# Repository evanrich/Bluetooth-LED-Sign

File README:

# Bluetooth LED Sign - Control Sure 3216 displays from your computer/phone via Bluetooth

The Bluetooth sign project started out originally from me wanting a wireless sign I could put in my car to tell drivers to get off my ass when they were following too close.    It started as just a daughter card that was shaped to connect directly to the back of a Sure 3216 (3mm) display.  I then wanted to be able to have a much larger display, and instead of buying 3216 boards at $24+ plus shipping, I went about designing the equivelent of 3x 3216 boards. 

The project has many uses, from digital cube/office name or status signs (out of office?) to vehicle/store signs.

**Source code**

* https://github.com/evanrich/Bluetooth-LED-Sign

**Licensing**<br />
<br /><span xmlns:dct="http://purl.org/dc/terms/" property="dct:title">Bluetooth LED Sign</span> by <a xmlns:cc="http://creativecommons.org/ns#" href="https://github.com/evanrich/Bluetooth-LED-Sign" property="cc:attributionName" rel="cc:attributionURL">Evan Richardson</a> is licensed under a <a rel="license" href="http://creativecommons.org/licenses/by-sa/3.0/">Creative Commons Attribution-ShareAlike 3.0 Unported License</a>.<br />Based on a work at <a xmlns:dct="http://purl.org/dc/terms/" href="https://code.google.com/p/ht1632c/" rel="dct:source">code.google.com</a>.

**Features**

* Small Size: 54x39mm ( 2.13" x 1.54")
* Custom LED Board is 15.15"3.20"
* Multiple mounting options: Controller plugs directly into back of Sure 3216 or custom 9616 boards
* Low Power: Controller operates around 50-80mA (needs to be tested) with a 2000mAh battery it can run >4 hours on single charge
* Wireless: BLUETOOTH!!  works up to 30+ feet away
* Charges/Runs via USB port (500mA only, 12V wall plug option being added)
* Fuel Guage IC has been added to allow reporting/displaying of remaining capacity (Code needs to be added however)
* Android and VB.NET apps can both control message color and speed, as well as looping the message until a new message is sent.
* Android: Voice Control - enter messages using your voice
* Android: History - Resend any of the last recently used messages by taping on it and hitting send.

**Known issues**

* Android:  If phone is in one orientation (Horizontal/Vertical) and you rotate your phone, it will dissconnect from the bluetooth module.  This is due to destroying and recreating the view, and therefore the bluetooth connection.  Need to figure how to fix this, or not allow rotation.
* New Arduino 1.0 code will not work with more than 2 displays
* Old Arduino 0023 code is slow when using text scaling (2 instead of 1)
* Android: If a Repeat is issued to the display, it will loop the text until a new message is sent.
* VB.NET: If a repeat and color change are issued, the display will not stop repeating until a new color is sent.

**To-Do**

* Develop some sort of user guide/documentation
* Finalize BOM
* Write Fuel Guage code to allow transmission or display of remaining battery capacity
* Prototype 96x16 board(Currently routing board traces)
* Confirm board/schematic for controller (device is 1/2 the size the first prototype was)
* Find or develop tool to allow updating firmware on the board (USB parts are there, so new firmware updates can be sent out to users)
* Other stuff

**Questions/Support**

* Original library/Sure 3216 information on Arduino.cc Forums @ [http://arduino.cc/forum/index.php/board,6.0.html](http://arduino.cc)

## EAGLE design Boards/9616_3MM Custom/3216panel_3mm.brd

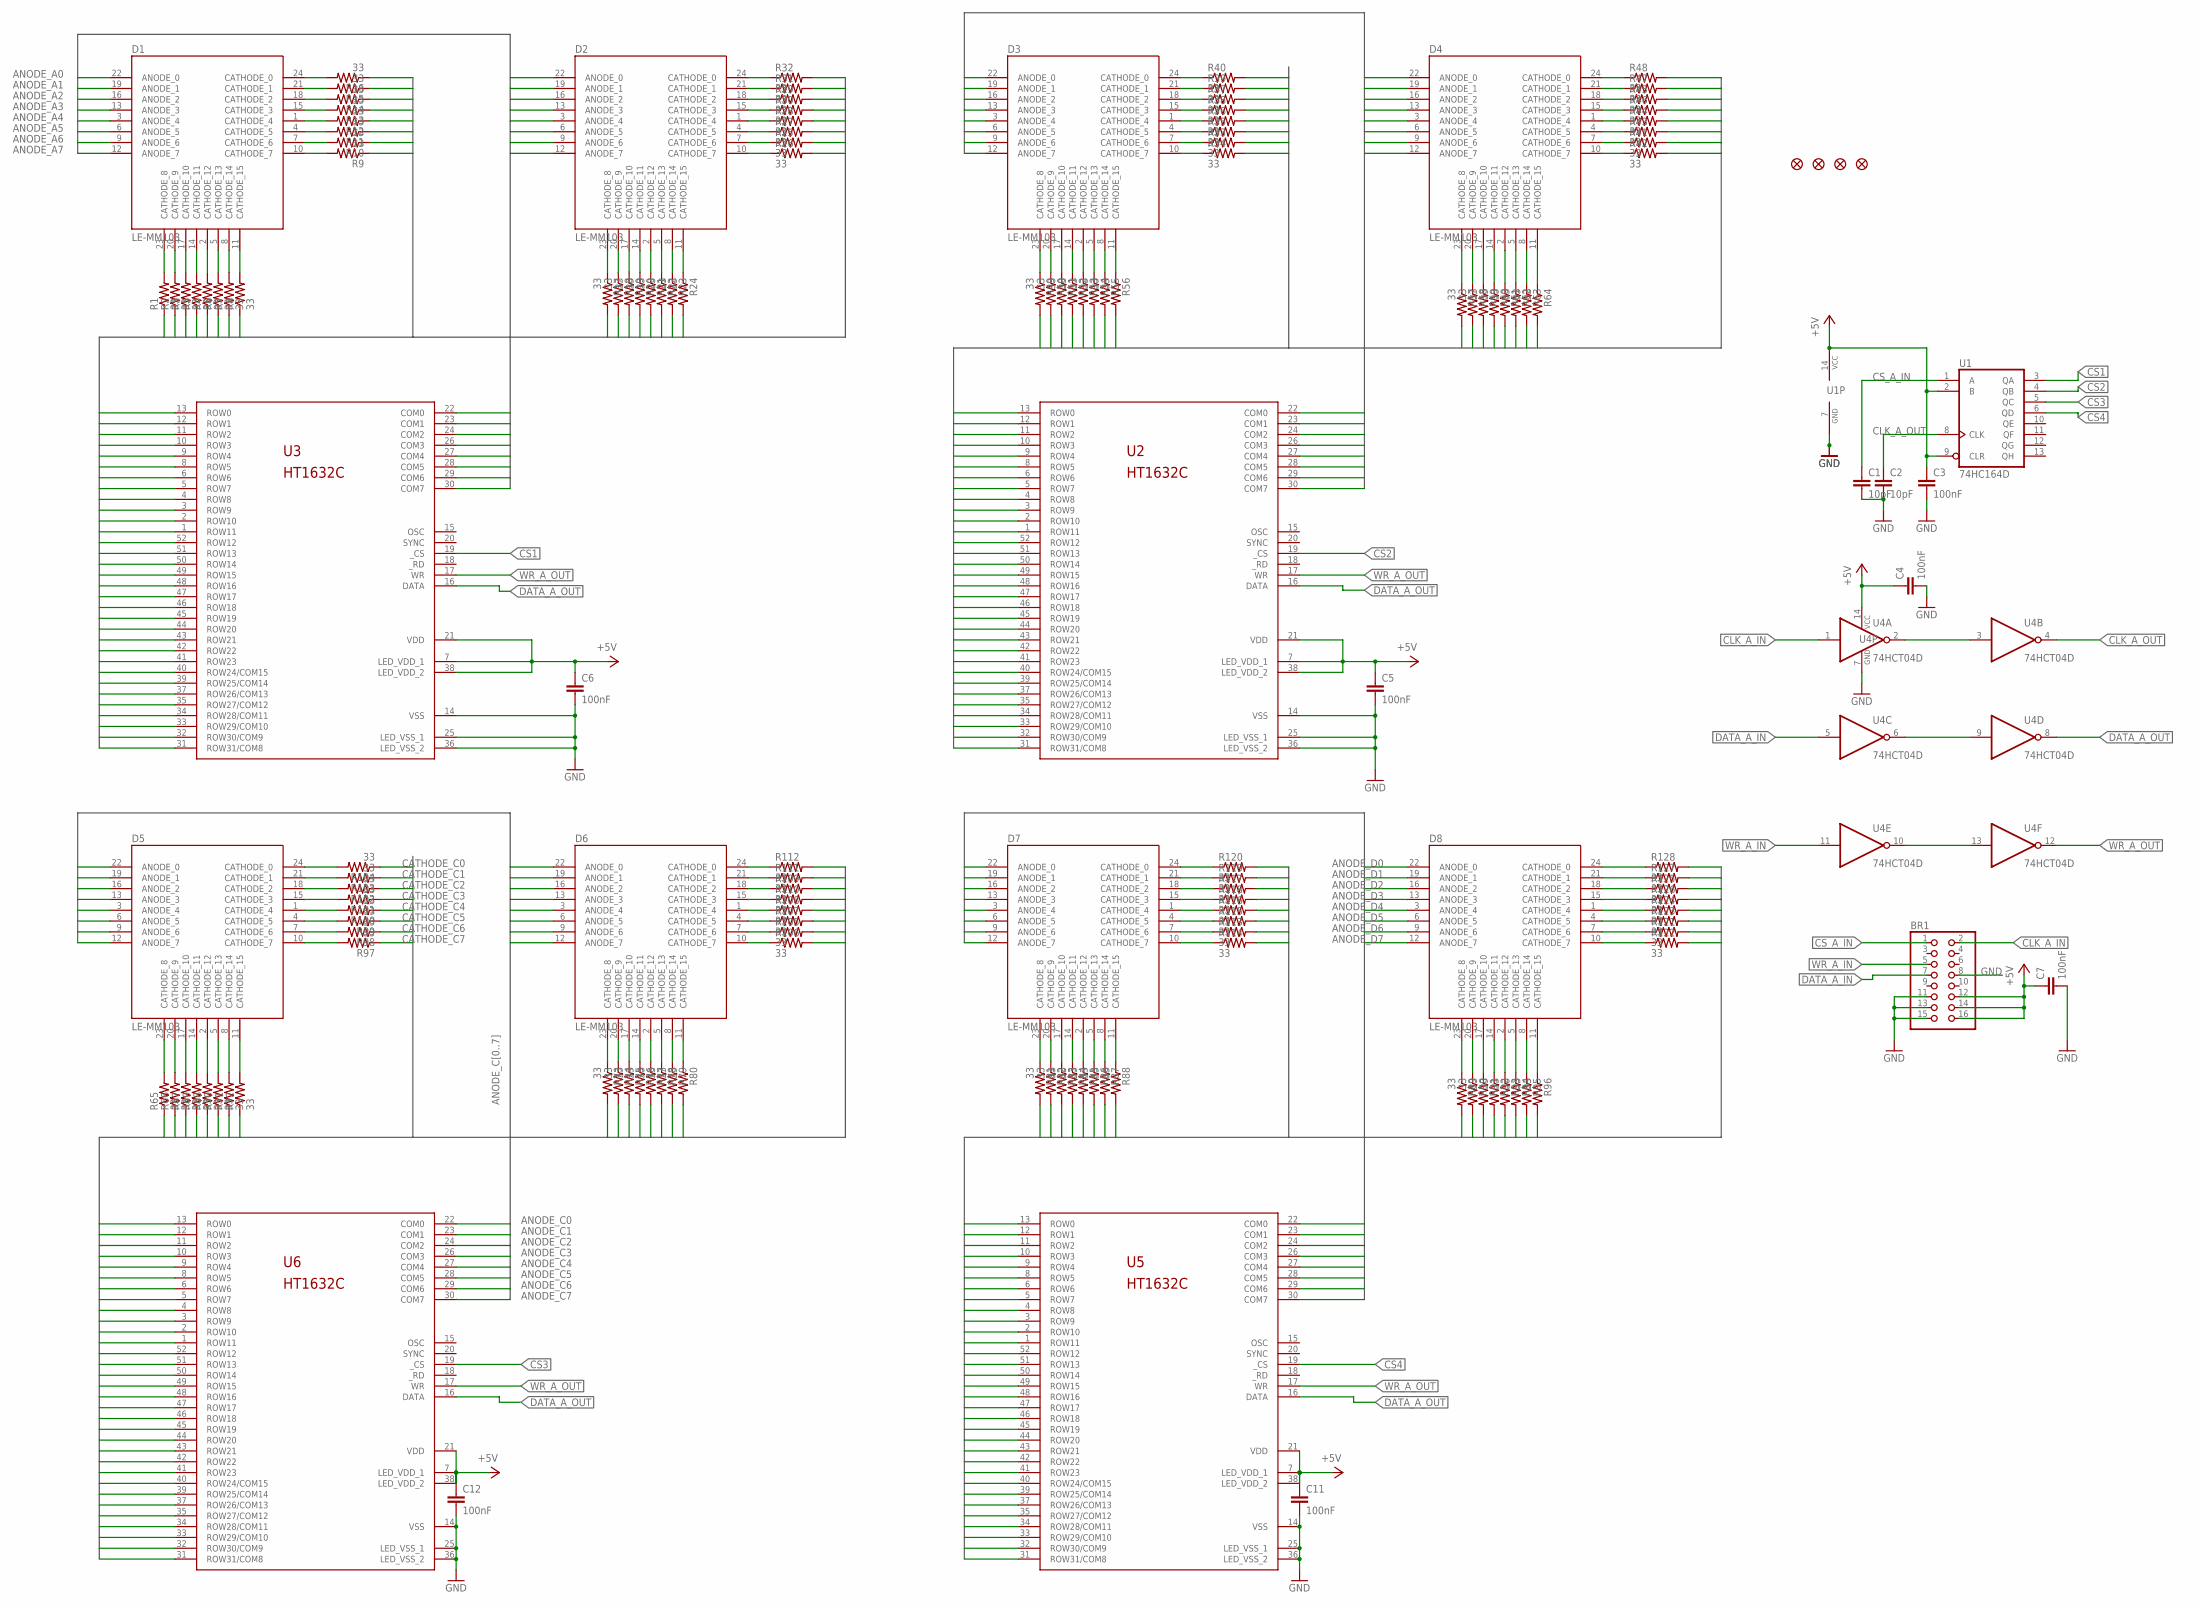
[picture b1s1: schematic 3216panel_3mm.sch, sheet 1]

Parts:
BR1: PINHD-2X8; 2X08
C1, C2: 10pF; 0805
C3, C4, C5, C6, C7, C11, C12: 100nF; 0805
D1, D2, D3, D4, D5, D6, D7, D8: LE-MM103; 8X8_3MM_LED_MATRIX
JP1, JP2, JP3, JP4: FIDUCIAL1X2.5; FIDUCIAL-1X2.5
R1, R2, R3, R4, R5, R6, R7, R8, R9, R10, R11, R12, R13, R14, R15, R16, R17, R18, R19, R20, R21, R22, R23, R24, R25, R26, R27, R28, R29, R30, R31, R32, R33, R34, R35, R36, R37, R38, R39, R40, R41, R42, R43, R44, R45, R46, R47, R48, R49, R50, R51, R52, R53, R54, R55, R56, R57, R58, R59, R60, R61, R62, R63, R64, R65, R66, R67, R68, R69, R70, R71, R72, R73, R74, R75, R76, R77, R78, R79, R80, R81, R82, R83, R84, R85, R86, R87, R88, R89, R90, R91, R92, R93, R94, R95, R96, R97, R98, R99, R100, R101, R102, R103, R104, R105, R106, R107, R108, R109, R110, R111, R112, R113, R114, R115, R116, R117, R118, R119, R120, R121, R122, R123, R124, R125, R126, R127, R128: 33; 0805
U1: 74HC164D; SO14
U2, U3, U5, U6: HT1632C; QFP52
U4: 74HCT04D; SO14

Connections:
+5V: BR1.12, BR1.14, BR1.16, C3.1, C4.1, C5.1, C6.1, C7.1, C11.1, C12.1, U1.2 (B), U1.9 (CLR), U1.14 (VCC), U2.7 (LED_VDD_1), U2.21 (VDD), U2.38 (LED_VDD_2), U3.7 (LED_VDD_1), U3.21 (VDD), U3.38 (LED_VDD_2), U4.14 (VCC), U5.7 (LED_VDD_1), U5.21 (VDD), U5.38 (LED_VDD_2), U6.7 (LED_VDD_1), U6.21 (VDD), U6.38 (LED_VDD_2); also elsewhere on the board
ANODE_A0: D1.22 (ANODE_0), D2.22 (ANODE_0), U3.22 (COM0)
ANODE_A1: D1.19 (ANODE_1), D2.19 (ANODE_1), U3.23 (COM1)
ANODE_A2: D1.16 (ANODE_2), D2.16 (ANODE_2), U3.24 (COM2)
ANODE_A3: D1.13 (ANODE_3), D2.13 (ANODE_3), U3.26 (COM3)
ANODE_A4: D1.3 (ANODE_4), D2.3 (ANODE_4), U3.27 (COM4)
ANODE_A5: D1.6 (ANODE_5), D2.6 (ANODE_5), U3.28 (COM5)
ANODE_A6: D1.9 (ANODE_6), D2.9 (ANODE_6), U3.29 (COM6)
ANODE_A7: D1.12 (ANODE_7), D2.12 (ANODE_7), U3.30 (COM7)
ANODE_B0: D3.22 (ANODE_0), D4.22 (ANODE_0), U2.22 (COM0)
ANODE_B1: D3.19 (ANODE_1), D4.19 (ANODE_1), U2.23 (COM1)
ANODE_B2: D3.16 (ANODE_2), D4.16 (ANODE_2), U2.24 (COM2)
ANODE_B3: D3.13 (ANODE_3), D4.13 (ANODE_3), U2.26 (COM3)
ANODE_B4: D3.3 (ANODE_4), D4.3 (ANODE_4), U2.27 (COM4)
ANODE_B5: D3.6 (ANODE_5), D4.6 (ANODE_5), U2.28 (COM5)
ANODE_B6: D3.9 (ANODE_6), D4.9 (ANODE_6), U2.29 (COM6)
ANODE_B7: D3.12 (ANODE_7), D4.12 (ANODE_7), U2.30 (COM7)
ANODE_C0: D5.22 (ANODE_0), D6.22 (ANODE_0), U6.22 (COM0)
ANODE_C1: D5.19 (ANODE_1), D6.19 (ANODE_1), U6.23 (COM1)
ANODE_C2: D5.16 (ANODE_2), D6.16 (ANODE_2), U6.24 (COM2)
ANODE_C3: D5.13 (ANODE_3), D6.13 (ANODE_3), U6.26 (COM3)
ANODE_C4: D5.3 (ANODE_4), D6.3 (ANODE_4), U6.27 (COM4)
ANODE_C5: D5.6 (ANODE_5), D6.6 (ANODE_5), U6.28 (COM5)
ANODE_C6: D5.9 (ANODE_6), D6.9 (ANODE_6), U6.29 (COM6)
ANODE_C7: D5.12 (ANODE_7), D6.12 (ANODE_7), U6.30 (COM7)
ANODE_D0: D7.22 (ANODE_0), D8.22 (ANODE_0), U5.22 (COM0)
ANODE_D1: D7.19 (ANODE_1), D8.19 (ANODE_1), U5.23 (COM1)
ANODE_D2: D7.16 (ANODE_2), D8.16 (ANODE_2), U5.24 (COM2)
ANODE_D3: D7.13 (ANODE_3), D8.13 (ANODE_3), U5.26 (COM3)
ANODE_D4: D7.3 (ANODE_4), D8.3 (ANODE_4), U5.27 (COM4)
ANODE_D5: D7.6 (ANODE_5), D8.6 (ANODE_5), U5.28 (COM5)
ANODE_D6: D7.9 (ANODE_6), D8.9 (ANODE_6), U5.29 (COM6)
ANODE_D7: D7.12 (ANODE_7), D8.12 (ANODE_7), U5.30 (COM7)
CATHODE_A0: R16.1, U3.13 (ROW0)
CATHODE_A1: R15.1, U3.12 (ROW1)
CATHODE_A2: R14.1, U3.11 (ROW2)
CATHODE_A3: R13.1, U3.10 (ROW3)
CATHODE_A4: R12.1, U3.9 (ROW4)
CATHODE_A5: R11.1, U3.8 (ROW5)
CATHODE_A6: R10.1, U3.6 (ROW6)
CATHODE_A7: R9.1, U3.5 (ROW7)
CATHODE_A8: R32.2, U3.4 (ROW8)
CATHODE_A9: R31.2, U3.3 (ROW9)
CATHODE_A10: R29.2, U3.2 (ROW10)
CATHODE_A11: R30.2, U3.1 (ROW11)
CATHODE_A12: R28.2, U3.52 (ROW12)
CATHODE_A13: R27.2, U3.51 (ROW13)
CATHODE_A14: R25.2, U3.50 (ROW14)
CATHODE_A15: R26.2, U3.49 (ROW15)
CATHODE_A16: R1.1, U3.48 (ROW16)
CATHODE_A17: R2.1, U3.47 (ROW17)
CATHODE_A18: R3.1, U3.46 (ROW18)
CATHODE_A19: R5.1, U3.45 (ROW19)
CATHODE_A20: R4.1, U3.44 (ROW20)
CATHODE_A21: R6.1, U3.43 (ROW21)
CATHODE_A22: R7.1, U3.42 (ROW22)
CATHODE_A23: R8.1, U3.41 (ROW23)
CATHODE_A24: R17.2, U3.40 (ROW24/COM15)
CATHODE_A25: R18.2, U3.39 (ROW25/COM14)
CATHODE_A26: R19.2, U3.37 (ROW26/COM13)
CATHODE_A27: R20.2, U3.35 (ROW27/COM12)
CATHODE_A28: R21.2, U3.34 (ROW28/COM11)
CATHODE_A29: R22.2, U3.33 (ROW29/COM10)
CATHODE_A30: R23.2, U3.32 (ROW30/COM9)
CATHODE_A31: R24.2, U3.31 (ROW31/COM8)
CATHODE_B0: R40.2, U2.13 (ROW0)
CATHODE_B1: R39.2, U2.12 (ROW1)
CATHODE_B2: R37.2, U2.11 (ROW2)
CATHODE_B3: R38.2, U2.10 (ROW3)
CATHODE_B4: R36.2, U2.9 (ROW4)
CATHODE_B5: R35.2, U2.8 (ROW5)
CATHODE_B6: R33.2, U2.6 (ROW6)
CATHODE_B7: R34.2, U2.5 (ROW7)
CATHODE_B8: R48.2, U2.4 (ROW8)
CATHODE_B9: R47.2, U2.3 (ROW9)
CATHODE_B10: R45.2, U2.2 (ROW10)
CATHODE_B11: R46.2, U2.1 (ROW11)
CATHODE_B12: R44.2, U2.52 (ROW12)
CATHODE_B13: R43.2, U2.51 (ROW13)
CATHODE_B14: R41.2, U2.50 (ROW14)
CATHODE_B15: R42.2, U2.49 (ROW15)
CATHODE_B16: R49.2, U2.48 (ROW16)
CATHODE_B17: R50.2, U2.47 (ROW17)
CATHODE_B18: R51.2, U2.46 (ROW18)
CATHODE_B19: R52.2, U2.45 (ROW19)
CATHODE_B20: R53.2, U2.44 (ROW20)
CATHODE_B21: R54.2, U2.43 (ROW21)
CATHODE_B22: R55.2, U2.42 (ROW22)
CATHODE_B23: R56.2, U2.41 (ROW23)
CATHODE_B24: R57.2, U2.40 (ROW24/COM15)
CATHODE_B25: R58.2, U2.39 (ROW25/COM14)
CATHODE_B26: R59.2, U2.37 (ROW26/COM13)
CATHODE_B27: R60.2, U2.35 (ROW27/COM12)
CATHODE_B28: R61.2, U2.34 (ROW28/COM11)
CATHODE_B29: R62.2, U2.33 (ROW29/COM10)
CATHODE_B30: R63.2, U2.32 (ROW30/COM9)
CATHODE_B31: R64.2, U2.31 (ROW31/COM8)
CATHODE_C0: R104.1, U6.13 (ROW0)
CATHODE_C1: R103.1, U6.12 (ROW1)
CATHODE_C2: R102.1, U6.11 (ROW2)
CATHODE_C3: R101.1, U6.10 (ROW3)
CATHODE_C4: R100.1, U6.9 (ROW4)
CATHODE_C5: R99.1, U6.8 (ROW5)
CATHODE_C6: R98.1, U6.6 (ROW6)
CATHODE_C7: R97.1, U6.5 (ROW7)
CATHODE_C8: R112.2, U6.4 (ROW8)
CATHODE_C9: R111.2, U6.3 (ROW9)
CATHODE_C10: R109.2, U6.2 (ROW10)
CATHODE_C11: R110.2, U6.1 (ROW11)
CATHODE_C12: R108.2, U6.52 (ROW12)
CATHODE_C13: R107.2, U6.51 (ROW13)
CATHODE_C14: R105.2, U6.50 (ROW14)
CATHODE_C15: R106.2, U6.49 (ROW15)
CATHODE_C16: R65.1, U6.48 (ROW16)
CATHODE_C17: R66.1, U6.47 (ROW17)
CATHODE_C18: R67.1, U6.46 (ROW18)
CATHODE_C19: R69.1, U6.45 (ROW19)
CATHODE_C20: R68.1, U6.44 (ROW20)
CATHODE_C21: R70.1, U6.43 (ROW21)
CATHODE_C22: R71.1, U6.42 (ROW22)
CATHODE_C23: R72.1, U6.41 (ROW23)
CATHODE_C24: R73.2, U6.40 (ROW24/COM15)
CATHODE_C25: R74.2, U6.39 (ROW25/COM14)
CATHODE_C26: R75.2, U6.37 (ROW26/COM13)
CATHODE_C27: R76.2, U6.35 (ROW27/COM12)
CATHODE_C28: R77.2, U6.34 (ROW28/COM11)
CATHODE_C29: R78.2, U6.33 (ROW29/COM10)
CATHODE_C30: R79.2, U6.32 (ROW30/COM9)
CATHODE_C31: R80.2, U6.31 (ROW31/COM8)
CATHODE_D0: R120.2, U5.13 (ROW0)
CATHODE_D1: R119.2, U5.12 (ROW1)
CATHODE_D2: R117.2, U5.11 (ROW2)
CATHODE_D3: R118.2, U5.10 (ROW3)
CATHODE_D4: R116.2, U5.9 (ROW4)
CATHODE_D5: R115.2, U5.8 (ROW5)
CATHODE_D6: R113.2, U5.6 (ROW6)
CATHODE_D7: R114.2, U5.5 (ROW7)
CATHODE_D8: R128.2, U5.4 (ROW8)
CATHODE_D9: R127.2, U5.3 (ROW9)
CATHODE_D10: R125.2, U5.2 (ROW10)
CATHODE_D11: R126.2, U5.1 (ROW11)
CATHODE_D12: R124.2, U5.52 (ROW12)
CATHODE_D13: R123.2, U5.51 (ROW13)
CATHODE_D14: R121.2, U5.50 (ROW14)
CATHODE_D15: R122.2, U5.49 (ROW15)
CATHODE_D16: R81.2, U5.48 (ROW16)
CATHODE_D17: R82.2, U5.47 (ROW17)
CATHODE_D18: R83.2, U5.46 (ROW18)
CATHODE_D19: R84.2, U5.45 (ROW19)
CATHODE_D20: R85.2, U5.44 (ROW20)
CATHODE_D21: R86.2, U5.43 (ROW21)
CATHODE_D22: R87.2, U5.42 (ROW22)
CATHODE_D23: R88.2, U5.41 (ROW23)
CATHODE_D24: R89.2, U5.40 (ROW24/COM15)
CATHODE_D25: R90.2, U5.39 (ROW25/COM14)
CATHODE_D26: R91.2, U5.37 (ROW26/COM13)
CATHODE_D27: R92.2, U5.35 (ROW27/COM12)
CATHODE_D28: R93.2, U5.34 (ROW28/COM11)
CATHODE_D29: R94.2, U5.33 (ROW29/COM10)
CATHODE_D30: R95.2, U5.32 (ROW30/COM9)
CATHODE_D31: R96.2, U5.31 (ROW31/COM8)
CLK_A_IN: BR1.2, U4.1 (I)
CLK_A_OUT: C2.1, U1.8 (CLK), U4.4 (O); also elsewhere on the board
CS1: U1.3 (QA), U3.19 (_CS)
CS2: U1.4 (QB), U2.19 (_CS)
CS3: U1.5 (QC), U6.19 (_CS)
CS4: U1.6 (QD), U5.19 (_CS); also elsewhere on the board
CS_A_IN: BR1.1, C1.1, U1.1 (A)
DATA_A_IN: BR1.7, U4.5 (I)
DATA_A_OUT: U2.16 (DATA), U3.16 (DATA), U4.8 (O), U5.16 (DATA), U6.16 (DATA); also elsewhere on the board
GND: BR1.8, BR1.11, BR1.13, BR1.15, C1.2, C2.2, C3.2, C4.2, C5.2, C6.2, C7.2, C11.2, C12.2, U1.7 (GND), U2.14 (VSS), U2.25 (LED_VSS_1), U2.36 (LED_VSS_2), U3.14 (VSS), U3.25 (LED_VSS_1), U3.36 (LED_VSS_2), U4.7 (GND), U5.14 (VSS), U5.25 (LED_VSS_1), U5.36 (LED_VSS_2), U6.14 (VSS), U6.25 (LED_VSS_1), U6.36 (LED_VSS_2); also elsewhere on the board
unnamed: D1.23 (CATHODE_8), R1.2
unnamed: D1.20 (CATHODE_9), R2.2
unnamed: D1.17 (CATHODE_10), R3.2
unnamed: D1.14 (CATHODE_11), R5.2
unnamed: D1.2 (CATHODE_12), R4.2
unnamed: D1.5 (CATHODE_13), R6.2
unnamed: D1.8 (CATHODE_14), R7.2
unnamed: D1.11 (CATHODE_15), R8.2
unnamed: D1.10 (CATHODE_7), R9.2
unnamed: D1.21 (CATHODE_1), R15.2
unnamed: D1.18 (CATHODE_2), R14.2
unnamed: D1.15 (CATHODE_3), R13.2
unnamed: D1.1 (CATHODE_4), R12.2
unnamed: D1.4 (CATHODE_5), R11.2
unnamed: D1.7 (CATHODE_6), R10.2
unnamed: D1.24 (CATHODE_0), R16.2
unnamed: D2.24 (CATHODE_0), R32.1
unnamed: D2.21 (CATHODE_1), R31.1
unnamed: D2.18 (CATHODE_2), R29.1
unnamed: D2.15 (CATHODE_3), R30.1
unnamed: D2.1 (CATHODE_4), R28.1
unnamed: D2.4 (CATHODE_5), R27.1
unnamed: D2.7 (CATHODE_6), R25.1
unnamed: D2.10 (CATHODE_7), R26.1
unnamed: D2.11 (CATHODE_15), R24.1
unnamed: D2.8 (CATHODE_14), R23.1
unnamed: D2.5 (CATHODE_13), R22.1
unnamed: D2.2 (CATHODE_12), R21.1
unnamed: D2.14 (CATHODE_11), R20.1
unnamed: D2.23 (CATHODE_8), R17.1
unnamed: D2.20 (CATHODE_9), R18.1
unnamed: D2.17 (CATHODE_10), R19.1
unnamed: D3.23 (CATHODE_8), R49.1
unnamed: D3.20 (CATHODE_9), R50.1
unnamed: D3.17 (CATHODE_10), R51.1
unnamed: D3.14 (CATHODE_11), R52.1
unnamed: D3.2 (CATHODE_12), R53.1
unnamed: D3.5 (CATHODE_13), R54.1
unnamed: D3.8 (CATHODE_14), R55.1
unnamed: D3.11 (CATHODE_15), R56.1
unnamed: D3.10 (CATHODE_7), R34.1
unnamed: D3.7 (CATHODE_6), R33.1
unnamed: D3.4 (CATHODE_5), R35.1
unnamed: D3.1 (CATHODE_4), R36.1
unnamed: D3.15 (CATHODE_3), R38.1
unnamed: D3.18 (CATHODE_2), R37.1
unnamed: D3.21 (CATHODE_1), R39.1
unnamed: D3.24 (CATHODE_0), R40.1
unnamed: D4.23 (CATHODE_8), R57.1
unnamed: D4.20 (CATHODE_9), R58.1
unnamed: D4.17 (CATHODE_10), R59.1
unnamed: D4.14 (CATHODE_11), R60.1
unnamed: D4.2 (CATHODE_12), R61.1
unnamed: D4.5 (CATHODE_13), R62.1
unnamed: D4.8 (CATHODE_14), R63.1
unnamed: D4.11 (CATHODE_15), R64.1
unnamed: D4.7 (CATHODE_6), R41.1
unnamed: D4.10 (CATHODE_7), R42.1
unnamed: D4.4 (CATHODE_5), R43.1
unnamed: D4.1 (CATHODE_4), R44.1
unnamed: D4.18 (CATHODE_2), R45.1
unnamed: D4.15 (CATHODE_3), R46.1
unnamed: D4.21 (CATHODE_1), R47.1
unnamed: D4.24 (CATHODE_0), R48.1
unnamed: D5.10 (CATHODE_7), R97.2
unnamed: D5.7 (CATHODE_6), R98.2
unnamed: D5.4 (CATHODE_5), R99.2
unnamed: D5.1 (CATHODE_4), R100.2
unnamed: D5.15 (CATHODE_3), R101.2
unnamed: D5.18 (CATHODE_2), R102.2
unnamed: D5.21 (CATHODE_1), R103.2
unnamed: D5.24 (CATHODE_0), R104.2
unnamed: D5.23 (CATHODE_8), R65.2
unnamed: D5.20 (CATHODE_9), R66.2
unnamed: D5.17 (CATHODE_10), R67.2
unnamed: D5.2 (CATHODE_12), R68.2
unnamed: D5.14 (CATHODE_11), R69.2
unnamed: D5.5 (CATHODE_13), R70.2
unnamed: D5.8 (CATHODE_14), R71.2
unnamed: D5.11 (CATHODE_15), R72.2
unnamed: D6.23 (CATHODE_8), R73.1
unnamed: D6.20 (CATHODE_9), R74.1
unnamed: D6.17 (CATHODE_10), R75.1
unnamed: D6.14 (CATHODE_11), R76.1
unnamed: D6.2 (CATHODE_12), R77.1
unnamed: D6.5 (CATHODE_13), R78.1
unnamed: D6.8 (CATHODE_14), R79.1
unnamed: D6.11 (CATHODE_15), R80.1
unnamed: D6.10 (CATHODE_7), R106.1
unnamed: D6.7 (CATHODE_6), R105.1
unnamed: D6.4 (CATHODE_5), R107.1
unnamed: D6.1 (CATHODE_4), R108.1
unnamed: D6.15 (CATHODE_3), R110.1
unnamed: D6.18 (CATHODE_2), R109.1
unnamed: D6.21 (CATHODE_1), R111.1
unnamed: D6.24 (CATHODE_0), R112.1
unnamed: D7.10 (CATHODE_7), R114.1
unnamed: D7.7 (CATHODE_6), R113.1
unnamed: D7.4 (CATHODE_5), R115.1
unnamed: D7.1 (CATHODE_4), R116.1
unnamed: D7.15 (CATHODE_3), R118.1
unnamed: D7.18 (CATHODE_2), R117.1
unnamed: D7.21 (CATHODE_1), R119.1
unnamed: D7.24 (CATHODE_0), R120.1
unnamed: D7.23 (CATHODE_8), R81.1
unnamed: D7.20 (CATHODE_9), R82.1
unnamed: D7.17 (CATHODE_10), R83.1
unnamed: D7.14 (CATHODE_11), R84.1
unnamed: D7.2 (CATHODE_12), R85.1
unnamed: D7.5 (CATHODE_13), R86.1
unnamed: D7.8 (CATHODE_14), R87.1
unnamed: D7.11 (CATHODE_15), R88.1
unnamed: D8.23 (CATHODE_8), R89.1
unnamed: D8.20 (CATHODE_9), R90.1
unnamed: D8.17 (CATHODE_10), R91.1
unnamed: D8.14 (CATHODE_11), R92.1
unnamed: D8.2 (CATHODE_12), R93.1
unnamed: D8.5 (CATHODE_13), R94.1
unnamed: D8.8 (CATHODE_14), R95.1
unnamed: D8.11 (CATHODE_15), R96.1
unnamed: D8.10 (CATHODE_7), R122.1
unnamed: D8.7 (CATHODE_6), R121.1
unnamed: D8.4 (CATHODE_5), R123.1
unnamed: D8.1 (CATHODE_4), R124.1
unnamed: D8.15 (CATHODE_3), R126.1
unnamed: D8.18 (CATHODE_2), R125.1
unnamed: D8.21 (CATHODE_1), R127.1
unnamed: D8.24 (CATHODE_0), R128.1
unnamed: U4.2 (O), U4.3 (I)
unnamed: U4.6 (O), U4.9 (I)
unnamed: U4.10 (O), U4.13 (I)
WR_A_IN: BR1.5, U4.11 (I)
WR_A_OUT: U2.17 (WR), U3.17 (WR), U4.12 (O), U5.17 (WR), U6.17 (WR); also elsewhere on the board

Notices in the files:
parts and their libraries:
SparkFun: Licensing: CC v3.0 Share-Alike You are welcome to use this library for commercial purposes.
